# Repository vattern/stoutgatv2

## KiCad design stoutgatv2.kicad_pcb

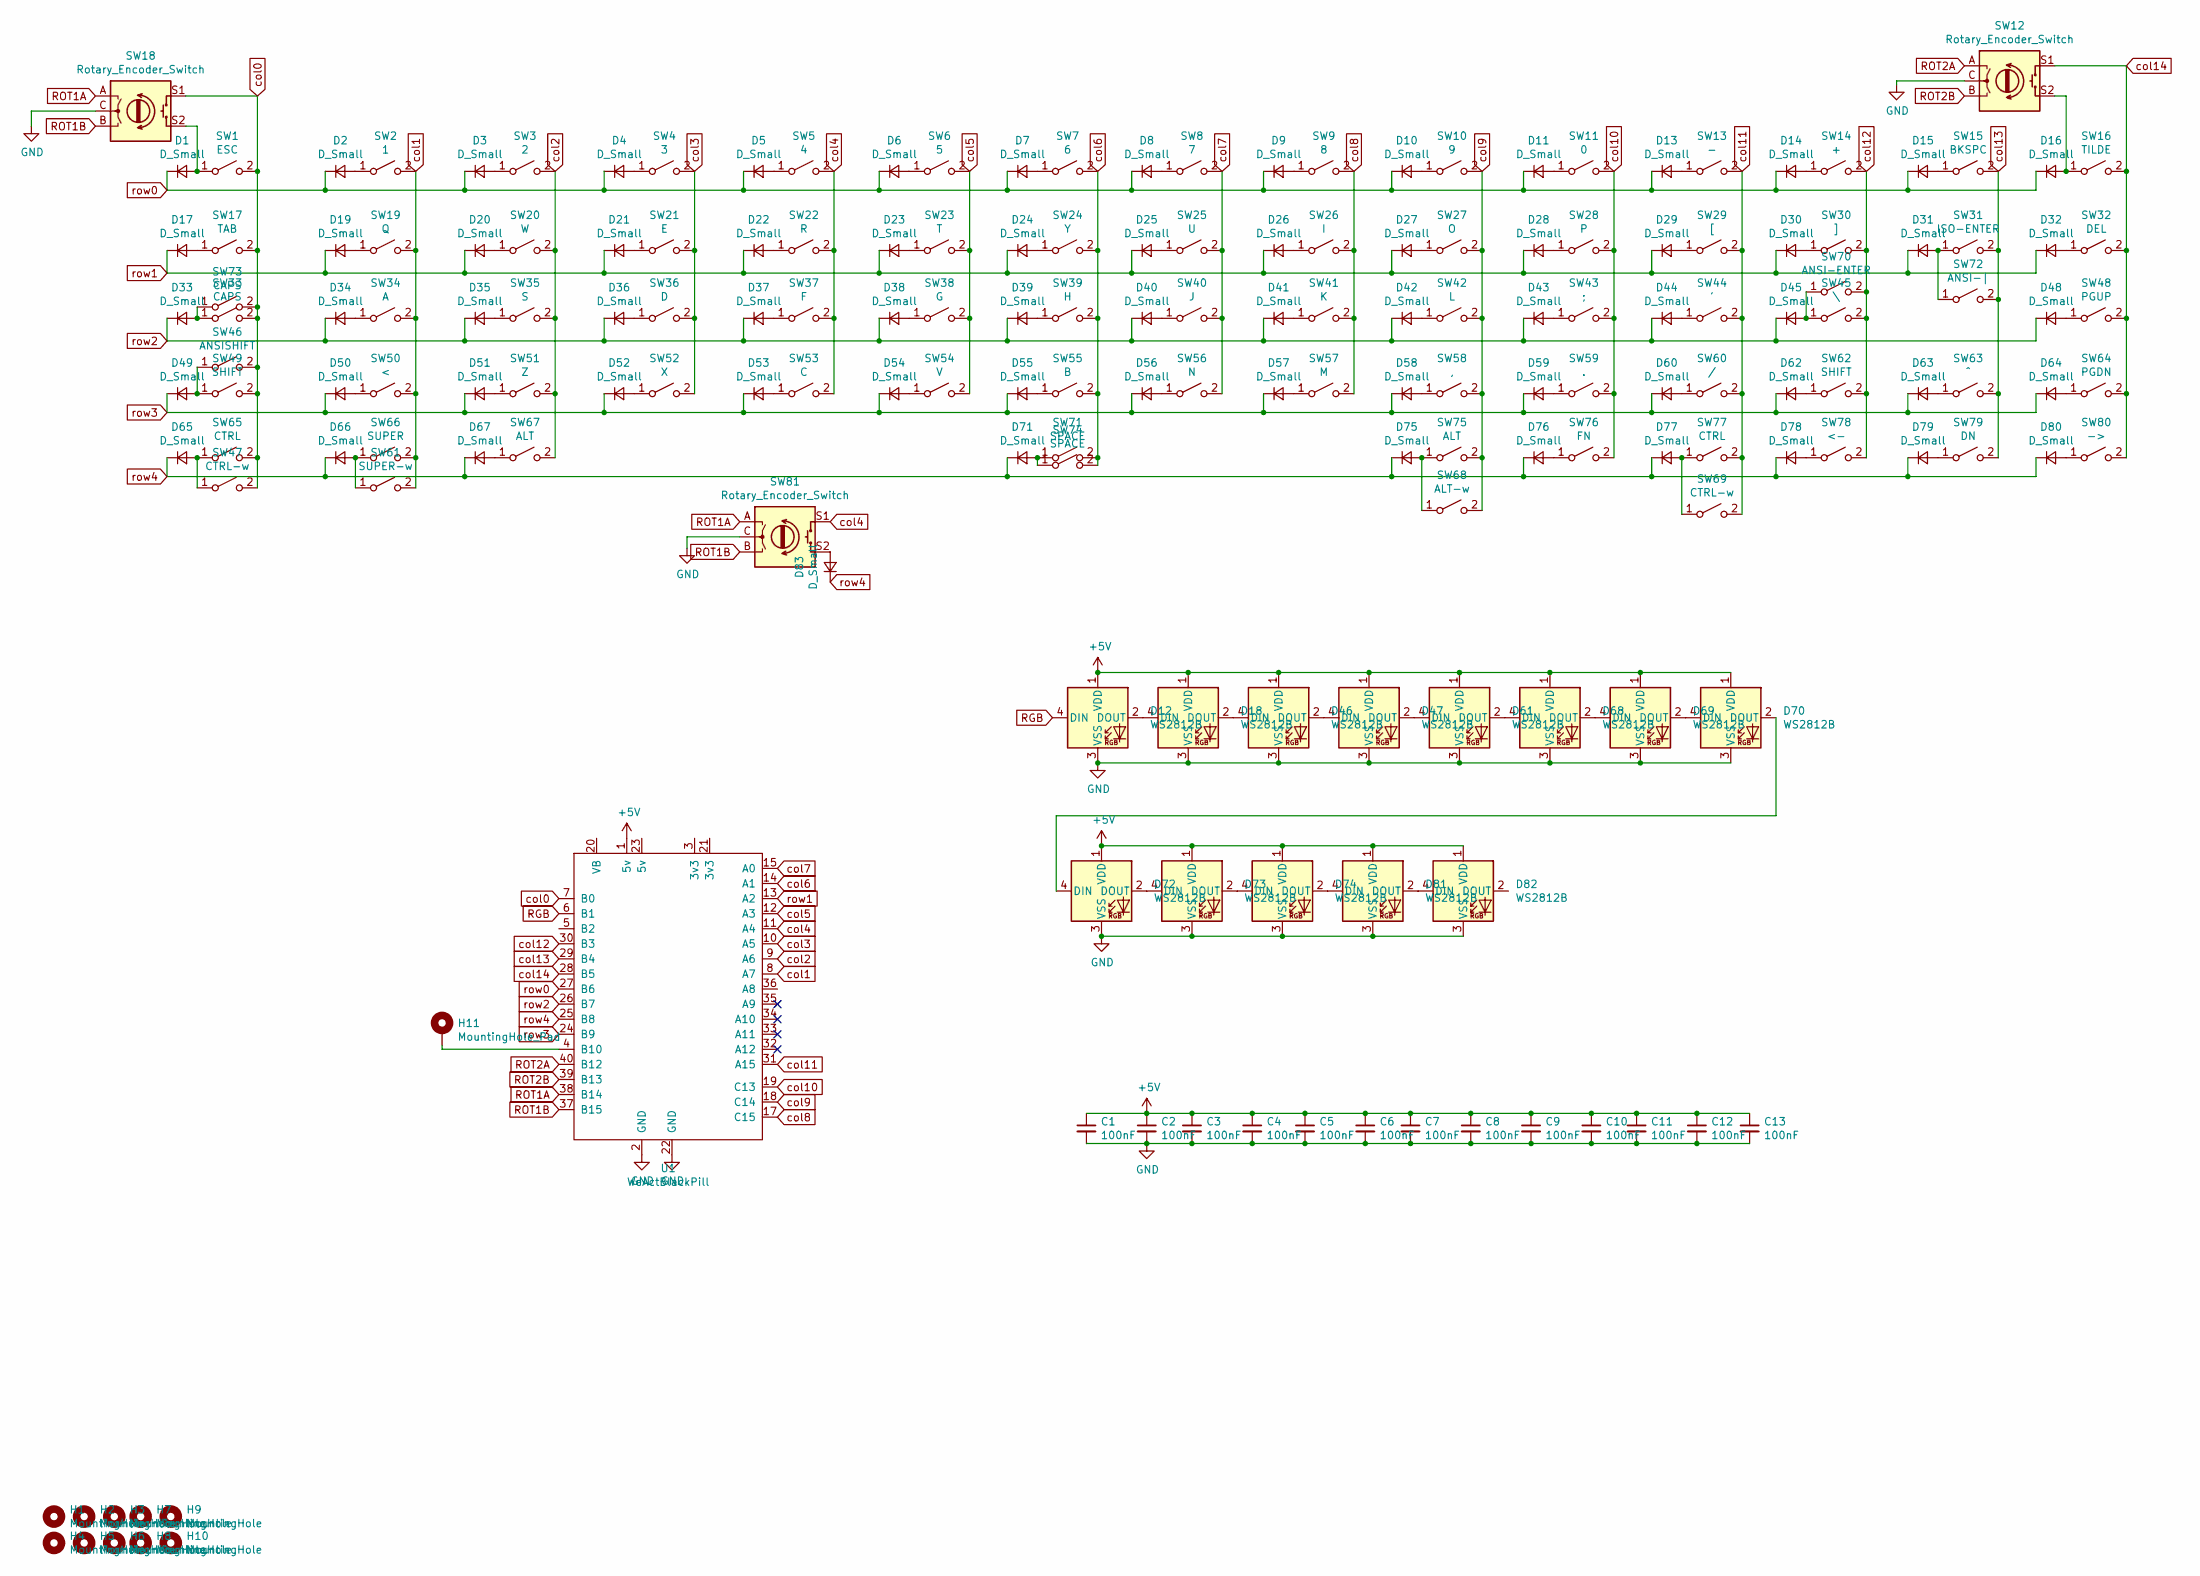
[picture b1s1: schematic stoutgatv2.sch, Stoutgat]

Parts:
C1, C2, C3, C4, C5, C6, C7, C8, C9, C10, C11, C12, C13: 100nF; C_0805_2012Metric
D1, D2, D3, D4, D5, D6, D7, D8, D9, D10, D11, D13, D14, D15, D16, D17, D19, D20, D21, D22, D23, D24, D25, D26, D27, D28, D29, D30, D31, D32, D33, D34, D35, D36, D37, D38, D39, D40, D41, D42, D43, D44, D45, D48, D49, D50, D51, D52, D53, D54, D55, D56, D57, D58, D59, D60, D62, D63, D64, D65, D66, D67, D71, D75, D76, D77, D78, D79, D80, D83: D_Small; D_DO-34_SOD68_P7.62mm_Horizontal
D12, D18, D46, D47, D61, D68, D69, D70, D72, D73, D74, D81, D82: WS2812B; LED_WS2812B_PLCC4_5.0x5.0mm_P3.2mm
H1, H2, H3, H4, H5, H6, H7, H8, H9, H10: MountingHole; MountingHole_3.2mm_M3
H11: MountingHole_Pad; TestPoint_Loop_D2.50mm_Drill1.0mm
SW1: ESC; SW_Cherry_MX_1.00u_PCB
SW2: 1; SW_Cherry_MX_1.00u_PCB
SW3: 2; SW_Cherry_MX_1.00u_PCB
SW4: 3; SW_Cherry_MX_1.00u_PCB
SW5: 4; SW_Cherry_MX_1.00u_PCB
SW6: 5; SW_Cherry_MX_1.00u_PCB
SW7: 6; SW_Cherry_MX_1.00u_PCB
SW8: 7; SW_Cherry_MX_1.00u_PCB
SW9: 8; SW_Cherry_MX_1.00u_PCB
SW10: 9; SW_Cherry_MX_1.00u_PCB
SW11: 0; SW_Cherry_MX_1.00u_PCB
SW12, SW18, SW81: Rotary_Encoder_Switch; RotaryEncoder_Alps_EC11E-Switch_Vertical_H20mm
SW13: -; SW_Cherry_MX_1.00u_PCB
SW14: +; SW_Cherry_MX_1.00u_PCB
SW15: BKSPC; SW_Cherry_MX_2.00u_PCB
SW16: TILDE; SW_Cherry_MX_1.00u_PCB
SW17: TAB; SW_Cherry_MX_1.50u_PCB
SW19: Q; SW_Cherry_MX_1.00u_PCB
SW20: W; SW_Cherry_MX_1.00u_PCB
SW21: E; SW_Cherry_MX_1.00u_PCB
SW22: R; SW_Cherry_MX_1.00u_PCB
SW23: T; SW_Cherry_MX_1.00u_PCB
SW24: Y; SW_Cherry_MX_1.00u_PCB
SW25: U; SW_Cherry_MX_1.00u_PCB
SW26: I; SW_Cherry_MX_1.00u_PCB
SW27: O; SW_Cherry_MX_1.00u_PCB
SW28: P; SW_Cherry_MX_1.00u_PCB
SW29: [; SW_Cherry_MX_1.00u_PCB
SW30: ]; SW_Cherry_MX_1.00u_PCB
SW31: ISO-ENTER; SW_Cherry_MX_ISOEnter_PCB
SW32: DEL; SW_Cherry_MX_1.00u_PCB
SW33: CAPS; SW_Cherry_MX_1.75u_PCB
SW34: A; SW_Cherry_MX_1.00u_PCB
SW35: S; SW_Cherry_MX_1.00u_PCB
SW36: D; SW_Cherry_MX_1.00u_PCB
SW37: F; SW_Cherry_MX_1.00u_PCB
SW38: G; SW_Cherry_MX_1.00u_PCB
SW39: H; SW_Cherry_MX_1.00u_PCB
SW40: J; SW_Cherry_MX_1.00u_PCB
SW41: K; SW_Cherry_MX_1.00u_PCB
SW42: L; SW_Cherry_MX_1.00u_PCB
SW43: ;; SW_Cherry_MX_1.00u_PCB
SW44: '; SW_Cherry_MX_1.00u_PCB
SW45: \\; SW_Cherry_MX_1.00u_PCB
SW46: ANSISHIFT; SW_Cherry_MX_2.25u_PCB
SW47, SW69: CTRL-w; SW_Cherry_MX_1.50u_PCB
SW48: PGUP; SW_Cherry_MX_1.00u_PCB
SW49: SHIFT; SW_Cherry_MX_1.25u_PCB
SW50: <; SW_Cherry_MX_1.00u_PCB
SW51: Z; SW_Cherry_MX_1.00u_PCB
SW52: X; SW_Cherry_MX_1.00u_PCB
SW53: C; SW_Cherry_MX_1.00u_PCB
SW54: V; SW_Cherry_MX_1.00u_PCB
SW55: B; SW_Cherry_MX_1.00u_PCB
SW56: N; SW_Cherry_MX_1.00u_PCB
SW57: M; SW_Cherry_MX_1.00u_PCB
SW58: ,; SW_Cherry_MX_1.00u_PCB
SW59: .; SW_Cherry_MX_1.00u_PCB
SW60: /; SW_Cherry_MX_1.00u_PCB
SW61: SUPER-w; SW_Cherry_MX_1.50u_PCB
SW62: SHIFT; SW_Cherry_MX_1.75u_PCB
SW63: ^; SW_Cherry_MX_1.00u_PCB
SW64: PGDN; SW_Cherry_MX_1.00u_PCB
SW65: CTRL; SW_Cherry_MX_1.25u_PCB
SW66: SUPER; SW_Cherry_MX_1.25u_PCB
SW67: ALT; SW_Cherry_MX_1.25u_PCB
SW68: ALT-w; SW_Cherry_MX_1.50u_PCB
SW70: ANSI-ENTER; SW_Cherry_MX_2.25u_PCB
SW71: SPACE; SW_Cherry_MX_6.25u_PCB
SW72: ANSI-|; SW_Cherry_MX_1.25u_PCB
SW73: CAPS; SW_Cherry_MX_1.25u_PCB
SW74: SPACE; SW_Cherry_MX_1.25u_PCB
SW75: ALT; SW_Cherry_MX_1.00u_PCB
SW76: FN; SW_Cherry_MX_1.00u_PCB
SW77: CTRL; SW_Cherry_MX_1.00u_PCB
SW78: <-; SW_Cherry_MX_1.00u_PCB
SW79: DN; SW_Cherry_MX_1.00u_PCB
SW80: ->; SW_Cherry_MX_1.00u_PCB
U1: WeActBlackPill; Blackpill

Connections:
+5V: C1.1, C2.1, C3.1, C4.1, C5.1, C6.1, C7.1, C8.1, C9.1, C10.1, C11.1, C12.1, C13.1, D12.1 (VDD), D18.1 (VDD), D46.1 (VDD), D47.1 (VDD), D61.1 (VDD), D68.1 (VDD), D69.1 (VDD), D70.1 (VDD), D72.1 (VDD), D73.1 (VDD), D74.1 (VDD), D81.1 (VDD), D82.1 (VDD), U1.1 (5v)
GND: C1.2, C2.2, C3.2, C4.2, C5.2, C6.2, C7.2, C8.2, C9.2, C10.2, C11.2, C12.2, C13.2, D12.3 (VSS), D18.3 (VSS), D46.3 (VSS), D47.3 (VSS), D61.3 (VSS), D68.3 (VSS), D69.3 (VSS), D70.3 (VSS), D72.3 (VSS), D73.3 (VSS), D74.3 (VSS), D81.3 (VSS), D82.3 (VSS), SW12.C, SW18.C, SW81.C, U1.2 (GND), U1.22 (GND)
unnamed: D1.2 (A), SW1.1 (A), SW18.S2
unnamed: D2.2 (A), SW2.1 (A)
unnamed: D3.2 (A), SW3.1 (A)
unnamed: D4.2 (A), SW4.1 (A)
unnamed: D5.2 (A), SW5.1 (A)
unnamed: D6.2 (A), SW6.1 (A)
unnamed: D7.2 (A), SW7.1 (A)
unnamed: D8.2 (A), SW8.1 (A)
unnamed: D9.2 (A), SW9.1 (A)
unnamed: D10.2 (A), SW10.1 (A)
unnamed: D11.2 (A), SW11.1 (A)
unnamed: D12.2 (DOUT), D18.4 (DIN)
unnamed: D13.2 (A), SW13.1 (A)
unnamed: D14.2 (A), SW14.1 (A)
unnamed: D15.2 (A), SW15.1 (A)
unnamed: D16.2 (A), SW12.S2, SW16.1 (A)
unnamed: D17.2 (A), SW17.1 (A)
unnamed: D18.2 (DOUT), D46.4 (DIN)
unnamed: D19.2 (A), SW19.1 (A)
unnamed: D20.2 (A), SW20.1 (A)
unnamed: D21.2 (A), SW21.1 (A)
unnamed: D22.2 (A), SW22.1 (A)
unnamed: D23.2 (A), SW23.1 (A)
unnamed: D24.2 (A), SW24.1 (A)
unnamed: D25.2 (A), SW25.1 (A)
unnamed: D26.2 (A), SW26.1 (A)
unnamed: D27.2 (A), SW27.1 (A)
unnamed: D28.2 (A), SW28.1 (A)
unnamed: D29.2 (A), SW29.1 (A)
unnamed: D30.2 (A), SW30.1 (A)
unnamed: D31.2 (A), SW31.1 (A), SW72.1 (A)
unnamed: D32.2 (A), SW32.1 (A)
unnamed: D33.2 (A), SW33.1 (A), SW73.1 (A)
unnamed: D34.2 (A), SW34.1 (A)
unnamed: D35.2 (A), SW35.1 (A)
unnamed: D36.2 (A), SW36.1 (A)
unnamed: D37.2 (A), SW37.1 (A)
unnamed: D38.2 (A), SW38.1 (A)
unnamed: D39.2 (A), SW39.1 (A)
unnamed: D40.2 (A), SW40.1 (A)
unnamed: D41.2 (A), SW41.1 (A)
unnamed: D42.2 (A), SW42.1 (A)
unnamed: D43.2 (A), SW43.1 (A)
unnamed: D44.2 (A), SW44.1 (A)
unnamed: D45.2 (A), SW45.1 (A), SW70.1 (A)
unnamed: D46.2 (DOUT), D47.4 (DIN)
unnamed: D47.2 (DOUT), D61.4 (DIN)
unnamed: D48.2 (A), SW48.1 (A)
unnamed: D49.2 (A), SW46.1 (A), SW49.1 (A)
unnamed: D50.2 (A), SW50.1 (A)
unnamed: D51.2 (A), SW51.1 (A)
unnamed: D52.2 (A), SW52.1 (A)
unnamed: D53.2 (A), SW53.1 (A)
unnamed: D54.2 (A), SW54.1 (A)
unnamed: D55.2 (A), SW55.1 (A)
unnamed: D56.2 (A), SW56.1 (A)
unnamed: D57.2 (A), SW57.1 (A)
unnamed: D58.2 (A), SW58.1 (A)
unnamed: D59.2 (A), SW59.1 (A)
unnamed: D60.2 (A), SW60.1 (A)
unnamed: D61.2 (DOUT), D68.4 (DIN)
unnamed: D62.2 (A), SW62.1 (A)
unnamed: D63.2 (A), SW63.1 (A)
unnamed: D64.2 (A), SW64.1 (A)
unnamed: D65.2 (A), SW47.1 (A), SW65.1 (A)
unnamed: D66.2 (A), SW61.1 (A), SW66.1 (A)
unnamed: D67.2 (A), SW67.1 (A)
unnamed: D68.2 (DOUT), D69.4 (DIN)
unnamed: D69.2 (DOUT), D70.4 (DIN)
unnamed: D70.2 (DOUT), D72.4 (DIN)
unnamed: D71.2 (A), SW71.1 (A), SW74.1 (A)
unnamed: D72.2 (DOUT), D73.4 (DIN)
unnamed: D73.2 (DOUT), D74.4 (DIN)
unnamed: D74.2 (DOUT), D81.4 (DIN)
unnamed: D75.2 (A), SW68.1 (A), SW75.1 (A)
unnamed: D76.2 (A), SW76.1 (A)
unnamed: D77.2 (A), SW69.1 (A), SW77.1 (A)
unnamed: D78.2 (A), SW78.1 (A)
unnamed: D79.2 (A), SW79.1 (A)
unnamed: D80.2 (A), SW80.1 (A)
unnamed: D81.2 (DOUT), D82.4 (DIN)
unnamed: D83.2 (A), SW81.S2
unnamed: H11.1, U1.4 (B10)
RGB: D12.4 (DIN), U1.6 (B1)
ROT1A: SW18.A, SW81.A, U1.38 (B14)
ROT1B: SW18.B, SW81.B, U1.37 (B15)
ROT2A: SW12.A, U1.40 (B12)
ROT2B: SW12.B, U1.39 (B13)
col0: SW1.2 (B), SW17.2 (B), SW18.S1, SW33.2 (B), SW46.2 (B), SW47.2 (B), SW49.2 (B), SW65.2 (B), SW73.2 (B), U1.7 (B0)
col1: SW2.2 (B), SW19.2 (B), SW34.2 (B), SW50.2 (B), SW61.2 (B), SW66.2 (B), U1.8 (A7)
col2: SW3.2 (B), SW20.2 (B), SW35.2 (B), SW51.2 (B), SW67.2 (B), U1.9 (A6)
col3: SW4.2 (B), SW21.2 (B), SW36.2 (B), SW52.2 (B), U1.10 (A5)
col4: SW5.2 (B), SW22.2 (B), SW37.2 (B), SW53.2 (B), SW81.S1, U1.11 (A4)
col5: SW6.2 (B), SW23.2 (B), SW38.2 (B), SW54.2 (B), U1.12 (A3)
col6: SW7.2 (B), SW24.2 (B), SW39.2 (B), SW55.2 (B), SW71.2 (B), SW74.2 (B), U1.14 (A1)
col7: SW8.2 (B), SW25.2 (B), SW40.2 (B), SW56.2 (B), U1.15 (A0)
col8: SW9.2 (B), SW26.2 (B), SW41.2 (B), SW57.2 (B), U1.17 (C15)
col9: SW10.2 (B), SW27.2 (B), SW42.2 (B), SW58.2 (B), SW68.2 (B), SW75.2 (B), U1.18 (C14)
col10: SW11.2 (B), SW28.2 (B), SW43.2 (B), SW59.2 (B), SW76.2 (B), U1.19 (C13)
col11: SW13.2 (B), SW29.2 (B), SW44.2 (B), SW60.2 (B), SW69.2 (B), SW77.2 (B), U1.31 (A15)
col12: SW14.2 (B), SW30.2 (B), SW45.2 (B), SW62.2 (B), SW70.2 (B), SW78.2 (B), U1.30 (B3)
col13: SW15.2 (B), SW31.2 (B), SW63.2 (B), SW72.2 (B), SW79.2 (B), U1.29 (B4)
col14: SW12.S1, SW16.2 (B), SW32.2 (B), SW48.2 (B), SW64.2 (B), SW80.2 (B), U1.28 (B5)
row0: D1.1 (K), D2.1 (K), D3.1 (K), D4.1 (K), D5.1 (K), D6.1 (K), D7.1 (K), D8.1 (K), D9.1 (K), D10.1 (K), D11.1 (K), D13.1 (K), D14.1 (K), D15.1 (K), D16.1 (K), U1.27 (B6)
row1: D17.1 (K), D19.1 (K), D20.1 (K), D21.1 (K), D22.1 (K), D23.1 (K), D24.1 (K), D25.1 (K), D26.1 (K), D27.1 (K), D28.1 (K), D29.1 (K), D30.1 (K), D31.1 (K), D32.1 (K), U1.13 (A2)
row2: D33.1 (K), D34.1 (K), D35.1 (K), D36.1 (K), D37.1 (K), D38.1 (K), D39.1 (K), D40.1 (K), D41.1 (K), D42.1 (K), D43.1 (K), D44.1 (K), D45.1 (K), D48.1 (K), U1.26 (B7)
row3: D49.1 (K), D50.1 (K), D51.1 (K), D52.1 (K), D53.1 (K), D54.1 (K), D55.1 (K), D56.1 (K), D57.1 (K), D58.1 (K), D59.1 (K), D60.1 (K), D62.1 (K), D63.1 (K), D64.1 (K), U1.24 (B9)
row4: D65.1 (K), D66.1 (K), D67.1 (K), D71.1 (K), D75.1 (K), D76.1 (K), D77.1 (K), D78.1 (K), D79.1 (K), D80.1 (K), D83.1 (K), U1.25 (B8)

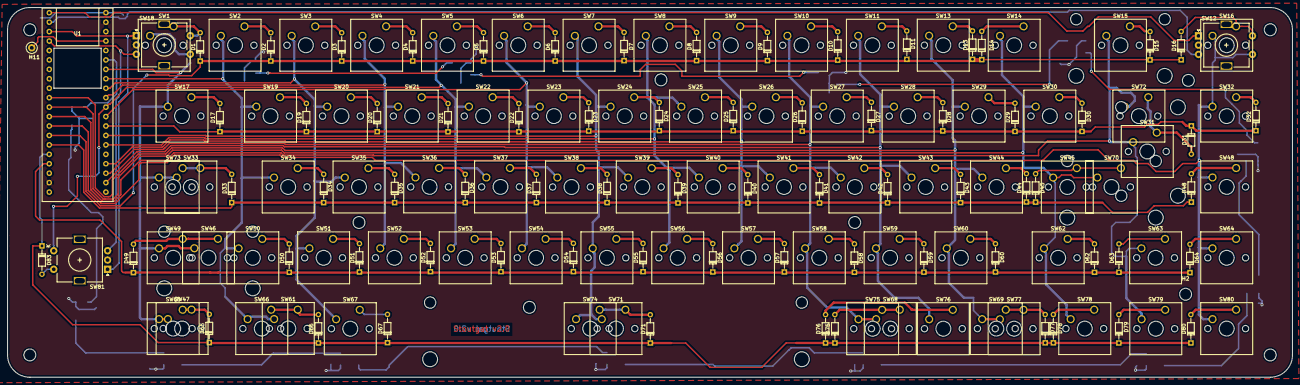
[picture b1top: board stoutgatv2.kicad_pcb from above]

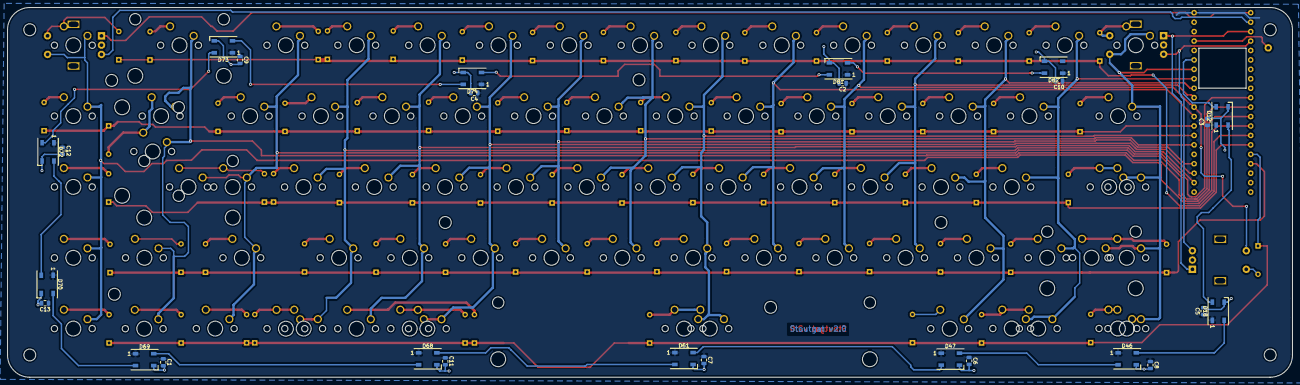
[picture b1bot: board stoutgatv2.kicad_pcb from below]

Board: 2 copper layers, 345.6 x 99.4 mm, 189 parts (26 on the bottom side), 110 nets.

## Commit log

2020-08-08 Add PCBs
2020-08-15 JLC tweaks
2020-09-04 Images
2020-09-12 adding case files
2020-09-20 Update cutout layer to no longer overlap mounting hardware
2021-02-21 case update
